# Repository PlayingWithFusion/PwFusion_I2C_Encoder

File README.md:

# PwFusion_I2C_Encoder

Are you looking for a way to take your project to the next level? Playing with Fusion's I2C Encoder board is the way to go! This device greatly simplifies connectivity to a microcontroller through the QWIIC system. The typical 5 wires required to use an encoder componet with a microcontroller can be reduced to one QWIIC cable. You can even chain multiple QWIIC devices together for maximum wiring efficiency! If that isn't enough, Playing with Fusion provides Arduino libraries to make writing code for these boards as easy as possible! Weather you are a beginner looking for a simple introduction to the world of hobbyist electronics or an advanced user looking for a rapid prototyping tool, Playing with Fusion's I2C Encoder is right for you!

## I2C Addresses

| ADR 0   |   ADR 1   |   Address |
| --- | --- | --- |
| uncut   |   uncut   |   0x01 |
| cut     |   uncut   |   0x02 |
| uncut   |   cut     |   0x03 |
| cut     |   cut     |   0x04 |

The Playing with Fusion I2C encoder board comes with 4 available I2C addresses, which can be easily selected by cutting the jumpers on the printed circuit board. This allows for 4 encoder boards to be used on the same QWIIC chain. If you would like more than 4, see docs/Programming Instructions and flash a modified firmware with additional I2C address options.

## Example Projects
RC Transmitter: https://github.com/PlayingWithFusion/RC_Transmitter

## Related
| Page | Link |
| --- | --- |
| PwFusion_I2C_Encoder_Arduino_Library:  | https://github.com/PlayingWithFusion/PwFusion_I2C_Encoder_Arduino_Library |
| PwFusion_Data_Transfer:                | https://github.com/PlayingWithFusion/PwFusion_Data_Transfer |
| IFB-40001 PwFusion_I2C_Encoder:   |  https://github.com/PlayingWithFusion/PwFusion_I2C_Encoder |
| IFB-40002 PwFusion_I2C_Joystick:  |  https://github.com/PlayingWithFusion/PwFusion_I2C_Joystick |
| IFB-40003 PwFusion_I2C_Switch:    |  https://github.com/PlayingWithFusion/PwFusion_I2C_Switch |
| IFB-40004 PwFusion_I2C_Buttons:   |  https://github.com/PlayingWithFusion/PwFusion_I2C_Buttons |

Visit https://www.playingwithfusion.com/ for more information.

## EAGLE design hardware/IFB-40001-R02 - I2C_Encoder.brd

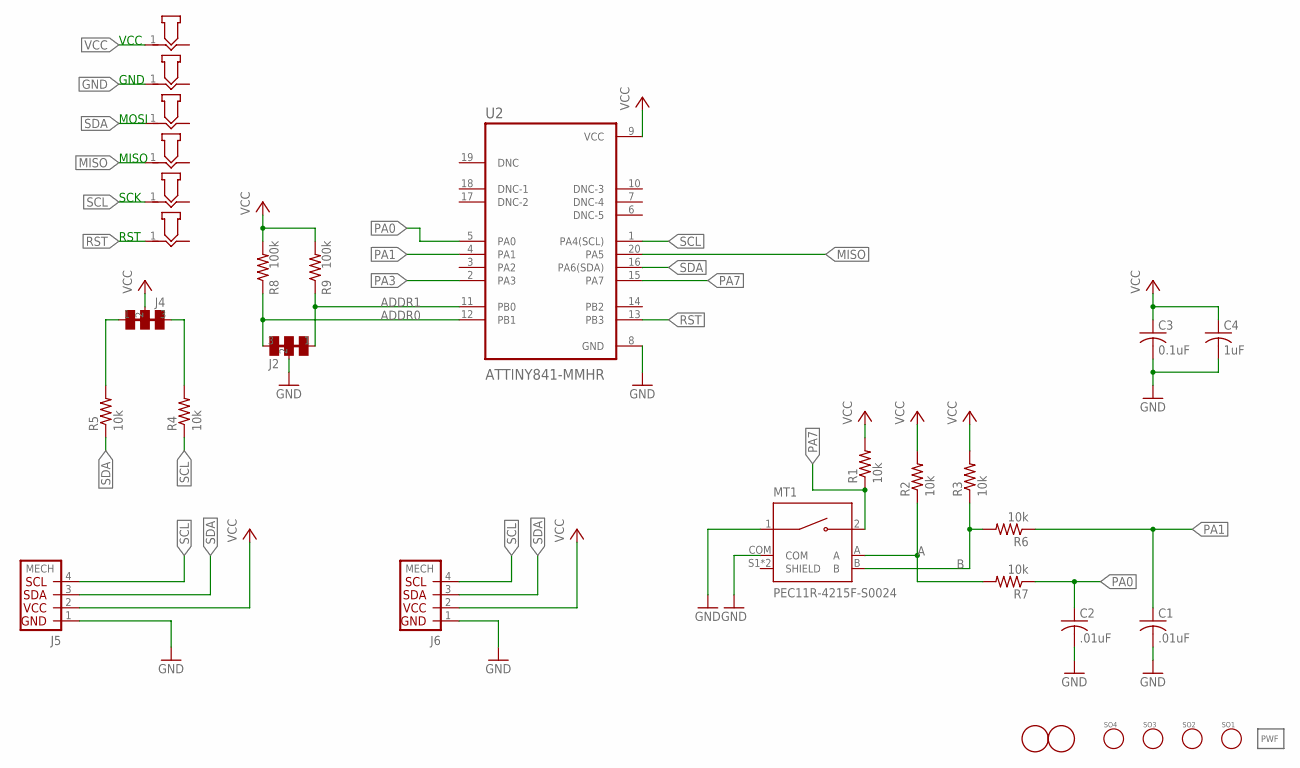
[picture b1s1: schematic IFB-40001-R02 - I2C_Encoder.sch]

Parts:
C1, C2: .01uF; C0603K
C3: 0.1uF; C0603K
C4: 1uF; C0603K
GND: POGO_PAD; P50_POGO_BOARD_CONTACT_12MIL
J2, J4: CUT_JUMPER_2X; SMT_2X_CUTTABLE_JUMPER
J5, J6: QWIICSIDE; SM04B-SRSS-TB
LOGO1: PWF_LOGOPWF-5MM-SS; LOGO_5MM_STEIN
MISO: POGO_PAD; P50_POGO_BOARD_CONTACT_12MIL
MOSI: POGO_PAD; P50_POGO_BOARD_CONTACT_12MIL
MT1: PEC11R-4215F-S0024; XDCR_PEC11R-4215F-S0024
R1, R2, R3, R4, R5, R6, R7: 10k; R0603
R8, R9: 100k; R0603
RST: POGO_PAD; P50_POGO_BOARD_CONTACT_12MIL
SCK: POGO_PAD; P50_POGO_BOARD_CONTACT_12MIL
SO1, SO2, SO3, SO4: STAND_OFFNO4_TIGHT; STANDOFF_NO4_TIGHT
U2: ATTINY841-MMHR; QFN45P300X300X85-21N
U$2, U$3: FIDUCIAL; FIDUCIAL_1MM
VCC: POGO_PAD; P50_POGO_BOARD_CONTACT_12MIL

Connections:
A: MT1.A, R2.1, R7.2
ADDR0: J2.3, R8.1, U2.12 (PB1)
ADDR1: J2.1, R9.1, U2.11 (PB0)
B: MT1.B, R3.1, R6.2
GND: C1.2, C2.2, C3.2, C4.2, GND.1, J2.2, J5.1, J6.1, MT1.1, MT1.COM, U2.8 (GND)
MISO: MISO.1, U2.20 (PA5)
unnamed: J4.1, R5.2
unnamed: J4.3, R4.2
PA0: C2.1, R7.1, U2.5 (PA0)
PA1: C1.1, R6.1, U2.4 (PA1)
PA3: U2.2 (PA3)
PA7: MT1.2, R1.1, U2.15 (PA7)
RST: RST.1, U2.13 (PB3)
SCL: J5.4, J6.4, R4.1, SCK.1, U2.1 (PA4(SCL))
SDA: J5.3, J6.3, MOSI.1, R5.1, U2.16 (PA6(SDA))
VCC: C3.1, C4.1, J4.2, J5.2, J6.2, R1.2, R2.2, R3.2, R8.2, R9.2, U2.9 (VCC), VCC.1

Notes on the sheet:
VCC
GND
MOSI
MISO
SCK
RST

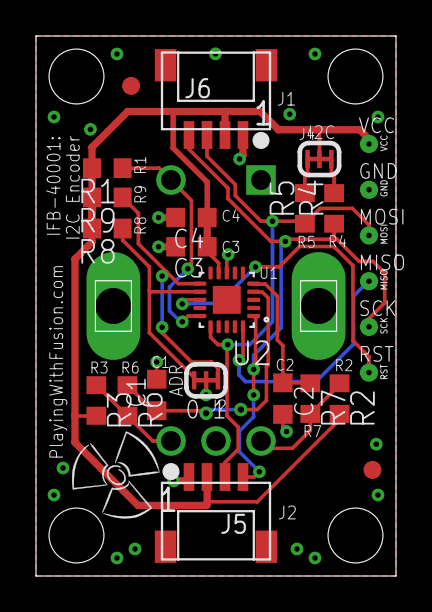
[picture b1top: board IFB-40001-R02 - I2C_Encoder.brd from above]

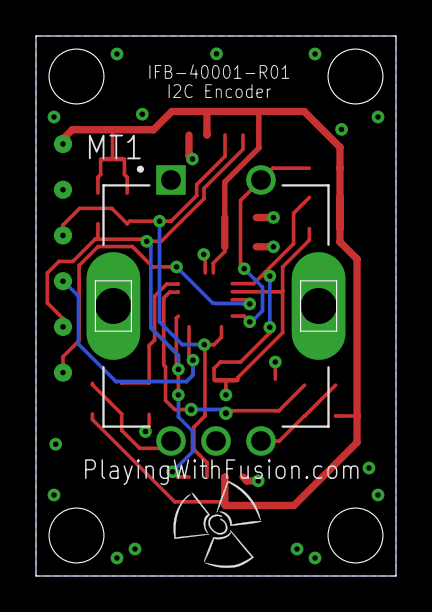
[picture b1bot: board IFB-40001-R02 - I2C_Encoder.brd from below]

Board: 2 copper layers, 20.0 x 30.0 mm, 33 parts (2 on the bottom side), 15 nets.

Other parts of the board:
LOGO2: PWF_LOGOPWF-6MM-SS; LOGO_5MM_STEIN

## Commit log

2023-10-01 Added firmware and readme
2023-10-08 hardware and links
2023-10-29 added programming instructions
2023-12-02 updated addresses
2023-12-02 updated hardware files
2024-06-28 Updated firmware flashing instructions
2024-06-28 fixed step numbering
2024-06-28 Added troubleshooting tip
